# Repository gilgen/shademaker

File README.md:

# Shademaker

An open source implementation of a stepper driven automated blind system.

## Required components
* Stepper motor (5:1 planetary geared)
* Arduino
* Hacked CNC shield
* 8825 stepper drivers
* Light sensor module
* Up/Down momentary switches
* On/Off toggle switch
* Relay
* 24v solenoid
* 8mm shaft couplers (no more than 16mm in diameter)
* 8mm rod
* 24v power supply

## WIP

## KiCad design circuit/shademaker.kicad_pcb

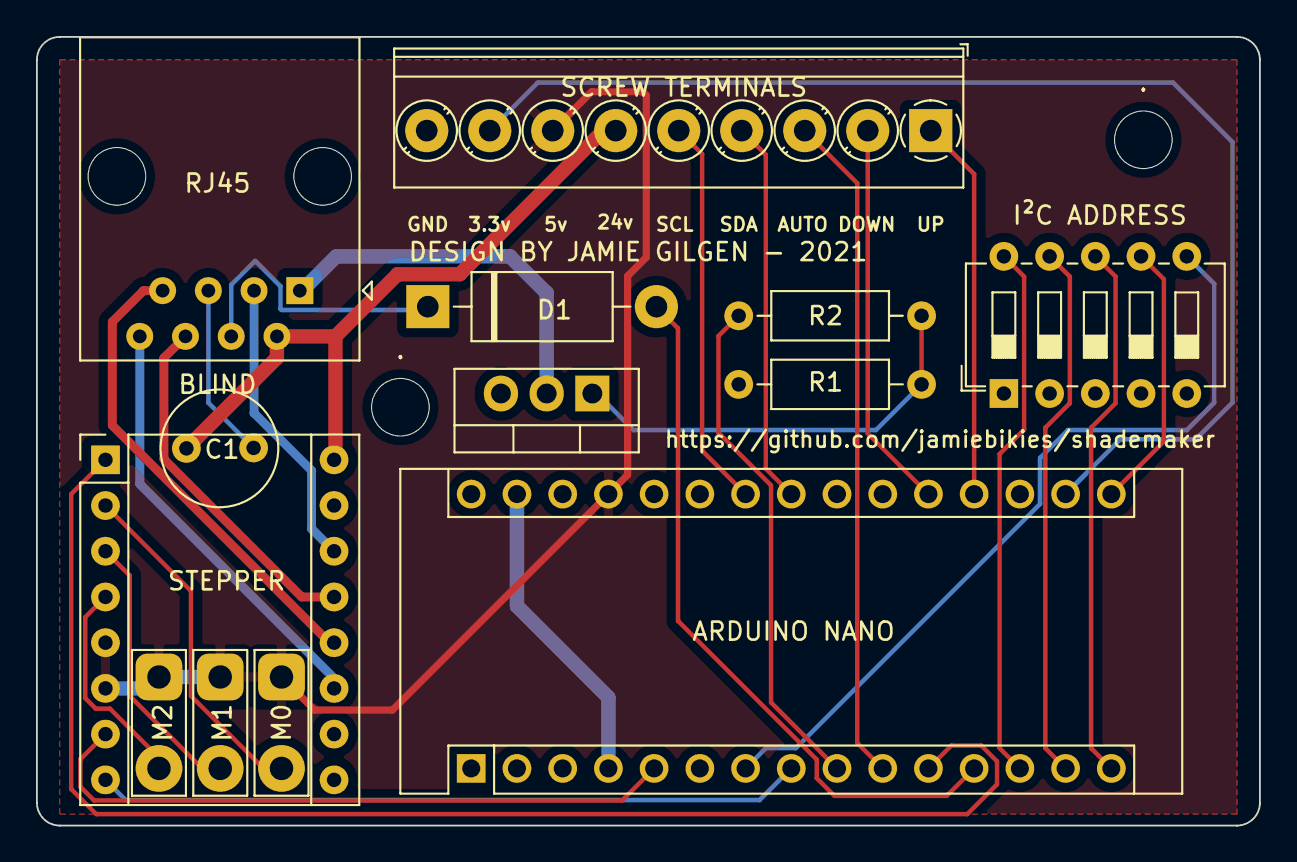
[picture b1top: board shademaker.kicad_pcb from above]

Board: 2 copper layers, 67.9 x 43.8 mm, 15 parts (0 on the bottom side), 29 nets.

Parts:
., .#2: MountingHole_3.2mm_M3
ARDUINO1: ARDUINO NANO; Arduino_Nano
C1: 100uf; C_Radial_D6.3mm_H7.0mm_P2.50mm
D1: D; D_DO-15_P12.70mm_Horizontal
M1, M2: Jumper_NO_Small; TestPoint_2Pads_Pitch5.08mm_Drill1.3mm
MO1: M0; TestPoint_2Pads_Pitch5.08mm_Drill1.3mm
Q1: IRLZ44N; TO-220-3_Vertical
R1: 10k; R_Axial_DIN0207_L6.3mm_D2.5mm_P10.16mm_Horizontal
R2: 2.2k; R_Axial_DIN0207_L6.3mm_D2.5mm_P10.16mm_Horizontal
RJ45: BLIND; RJ45_Amphenol_54602-x08_Horizontal
SCREW1: SCREW TERMINALS; TerminalBlock_Phoenix_PT-1,5-9-3.5-H_1x09_P3.50mm_Horizontal
STEPPER1: STEPPER; Pololu_Breakout-16_15.2x20.3mm
SW1: I²C ADDRESS; SW_DIP_SPSTx05_Slide_6.7x14.26mm_W7.62mm_P2.54mm_LowProfile

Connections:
3.3v: ARDUINO1.17, SCREW1.8
+5V: ARDUINO1.27, M1.1, M2.1, MO1.1, SCREW1.7, STEPPER1.5, STEPPER1.6
AUTO: ARDUINO1.10, SCREW1.3
DOWN: ARDUINO1.20, SCREW1.2
GND: ARDUINO1.4, ARDUINO1.29, C1.2, Q1.3, R1.2, RJ45.5, SCREW1.9, STEPPER1.9, STEPPER1.15, SW1.1, SW1.2, SW1.3, SW1.4, SW1.5
I2C_0: ARDUINO1.13, SW1.10
I2C_1: ARDUINO1.14, SW1.9
I2C_2: ARDUINO1.15, SW1.8
I2C_3: ARDUINO1.16, SW1.7
I2C_4: ARDUINO1.7, SW1.6
I2C_SCL: ARDUINO1.24, SCREW1.5
I2C_SDA: ARDUINO1.23, SCREW1.4
unnamed: ARDUINO1.12, D1.2
unnamed: Q1.1, R1.1, R2.2
SOLENOID+: C1.1, RJ45.2, SCREW1.6, STEPPER1.16
SOLENOID-: Q1.2, RJ45.1
SOLENOID_PWM: ARDUINO1.9, R2.1
STEPPER_1A(cat5green): RJ45.6, STEPPER1.13
STEPPER_1B(cat5brownwhite): RJ45.7, STEPPER1.12
STEPPER_2A(cat5greenwhite): RJ45.3, STEPPER1.14
STEPPER_2B(browncat5): RJ45.8, STEPPER1.11
STEPPER_DIR: ARDUINO1.8, STEPPER1.8
STEPPER_EN: ARDUINO1.11, STEPPER1.1
STEPPER_M0: MO1.2, STEPPER1.2
STEPPER_M1: M1.2, STEPPER1.3
STEPPER_M2: M2.2, STEPPER1.4
STEPPER_STEP: ARDUINO1.5, STEPPER1.7
STOP_SWITCH: D1.1, RJ45.4
UP: ARDUINO1.19, SCREW1.1

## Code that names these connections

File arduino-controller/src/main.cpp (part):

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// Pin 0 not used
// Pin 1 not used
#define STEP_PIN    2
#define I2C_4       4
#define DIRECTION   5
#define SOLENOID    6
#define AUTO_MODE   7
#define ENABLE_PIN  8
#define STOP_PIN    9
#define I2C_0       10
#define I2C_1       11
#define I2C_2       12
#define I2C_3       13
#define UP_PIN      A0
#define DOWN_PIN    A1
#define TEMPERATURE A2
#define LIGHT       A3
#define I2C_SDA     A4
#define I2C_SCL     A5

// Stepper driver modules
#define DRV8825 0
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  pinMode(DOWN_PIN, INPUT_PULLUP);
  pinMode(LIGHT, INPUT_PULLUP);
  pinMode(AUTO_MODE, INPUT_PULLUP);
  pinMode(I2C_0, INPUT_PULLUP);
  pinMode(I2C_1, INPUT_PULLUP);
  pinMode(I2C_2, INPUT_PULLUP);
  pinMode(I2C_3, INPUT_PULLUP);
  pinMode(I2C_4, INPUT_PULLUP);
}

void initializeFSMTransitions() {
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
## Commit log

2020-09-16 Pretty much fully functional
2020-09-17 Refactors
2020-09-17 Auto mode improvements
2021-03-24 Added model stls and 3mfs
2021-03-29 PCB and circuit
2021-03-29 Circuit + PCB
2021-04-01 Cleanup
2021-04-05 Add forward declarations
2021-04-14 Initial drop of web client
2021-04-14 WIP: Handle blind update events
2021-04-15 Starting to get frontend setup
2021-04-15 Remove .pyc
2021-04-15 Add platform.io setup to project
2021-04-15 Move things around
2021-04-15 Update express endpoints for bin dir
2021-04-15 Fix weird names on stl files
2021-04-15 A bit of cleanup. Change auto interval to 5h
2021-04-15 Don't log to serial with an invalid command. Causes blips in motor movement
2021-04-15 Use smbus2
2021-04-15 Make python script executable
2021-04-15 Fix bug
2021-04-15 Move circuit into root of project
2021-04-16 Setup react + express app for production deploy
2021-04-16 Fix up the stats return when homing
2021-04-16 Got a set of controls working for each blind set
2021-04-16 Send a STOP when the same command is received
2021-04-16 Getting the slider UI working
2021-04-16 More styling of the UI
2021-04-19 Cleaning up the react app
2021-04-21 Implement raspberry based auto control
2021-04-21 Move auto states fetch into its own file
2021-04-21 Implement auto mode toggle
2021-04-21 Auto mode styling
2021-04-21 Remove bin/.auto-states from source control
2021-04-21 Update all auto sensors involved when a command is sent
2021-04-23 Add settings functionality
2021-04-23 Use some better variable names in blind i2c command handlers
2021-04-23 Remove stop button functionality. It isn't necessary.
2021-04-23 Add forever up, forever down, and store commands for blind height setup
2021-04-23 Settings mode off by default
2021-04-23 Clear tick interval on unmount
2021-04-23 Auto updates can only happen every 5 hours
2021-04-23 When updating auto mode, set the last command at to be 10 hours ago so auto commands will run next auto heartbeat
2021-04-23 Don't update auto toggle via tick for a few seconds after updating it manually. It messes with things.
2021-04-23 Commands as consts for friendlier code
2021-04-23 Clear the auto timeout when unmounting a blindset slider
